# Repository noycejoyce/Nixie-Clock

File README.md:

# Noyce Joyce - Nixie Clock

## PCB design

The printed circuit board was designed in pre-released KiCAD 5.99 available at [nightly build](https://kicad-downloads.s3.cern.ch/index.html?prefix=windows/nightly/).

The core of the board is IoT Bluetooth chip from Nordic Semi nRF52832 which drives Nixie tubes IN-12 statically via nine shift registers.

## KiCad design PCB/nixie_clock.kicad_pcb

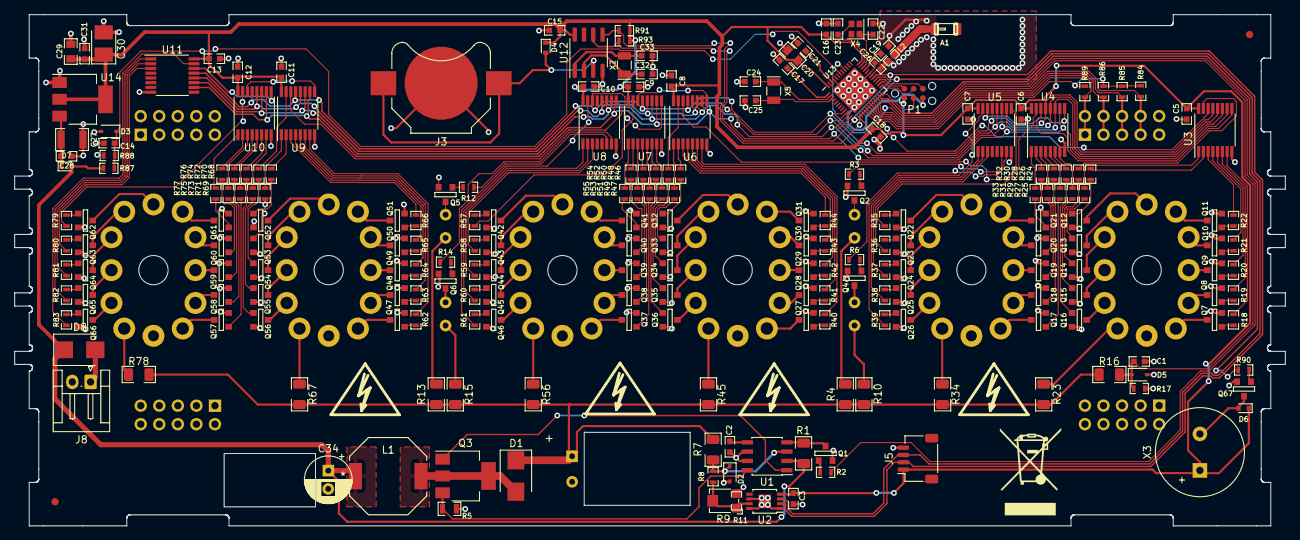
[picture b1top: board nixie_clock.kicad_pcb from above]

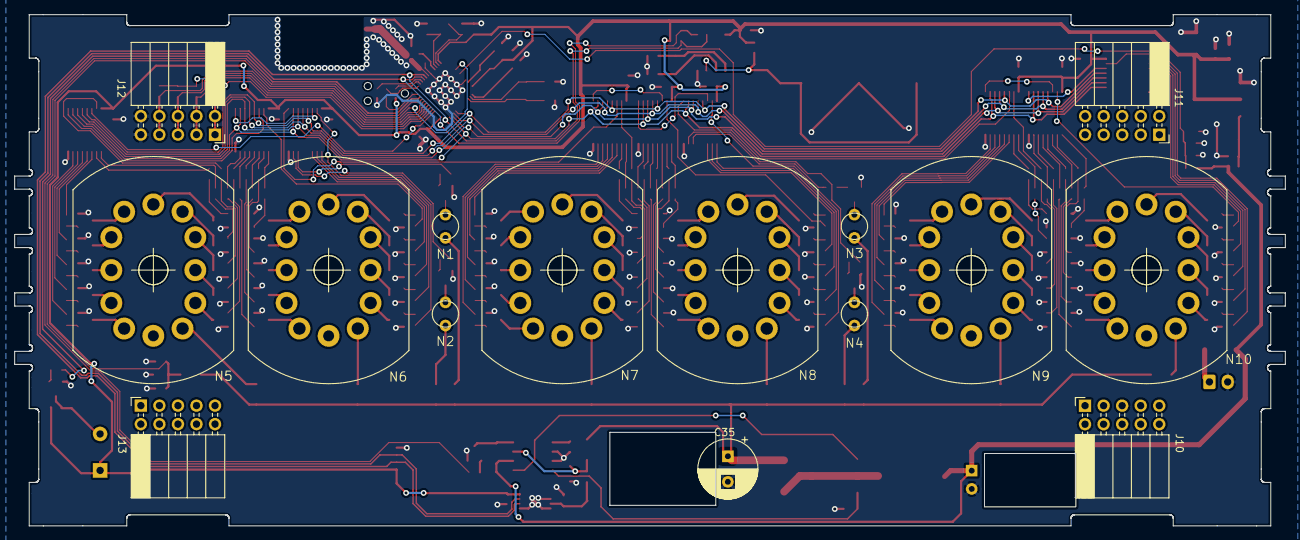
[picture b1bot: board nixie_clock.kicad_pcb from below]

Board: 2 copper layers, 174.0 x 70.0 mm, 247 parts (15 on the bottom side), 258 nets.

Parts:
A1: 2450AT18B100E; 2450A
C1, C2, C3, C5, C6, C7, C8, C9, C10, C11, C12, C13, C14, C17, C28, C31: 100n/50V; C_0603
C15, C16, C18, C21: 1u/25V; C_0603
C19: 100p; C_0603
C20, C29: 22u/6.3V; C_0805
C22, C23, C24, C25, C32, C33: 12p; C_0603
C26: 0.8p; C_0402
C27: 10u/35V; C_1210
C30: 100u/6.3V; CP_Tantalum_Case-B_EIA-3528-21_Reflow
C34: 100u/16V; CP_Radial_D6.3mm_P2.50mm
C35: 2.2u/400V; CP_Radial_D8.0mm_P3.50mm
D1, D8: ES2G; D_SMB_Standard
D2, D3, D5: MM3Z3V3T1G; D_SOD-323
D4, D6, D7: BAT42XV2; D_SOD-523
J1, J2: FiducialMark; AssemblyMark_1.0mm
J3: CR1225; BatteryHolder_Harwin_S8201R_1x12mm
J5: CONN_01X04; JST_SH_SM04B-SRSS-TB_1x04-1MP_P1.00mm_Horizontal
J8: CONN_01X02; JST_EH_S2B-EH_1x02_P2.50mm_Horizontal
J10, J11, J12, J13: CONN_02X05; PinSocket_2x05_P2.54mm_Horizontal
L1: SRU1038-101Y; L_Bourns_SRU1038
L2: 3.9nH; L_0402
N1, N2, N3, N4: IN-3; russian-nixies-IN-6
N5, N6, N7, N8, N9, N10: IN-12A; russian-nixies-IN-12
P1: TC2030-SWD; Tag-Connect_TC2030-IDC-NL
Q1, Q2, Q4, Q5, Q6, Q7, Q8, Q9, Q10, Q11, Q12, Q13, Q14, Q15, Q16, Q17, Q18, Q19, Q20, Q21, Q22, Q23, Q24, Q25, Q26, Q27, Q28, Q29, Q30, Q31, Q32, Q33, Q34, Q35, Q36, Q37, Q38, Q39, Q40, Q41, Q42, Q43, Q44, Q45, Q46, Q47, Q48, Q49, Q50, Q51, Q52, Q53, Q54, Q55, Q56, Q57, Q58, Q59, Q60, Q61, Q62, Q63, Q64, Q65, Q66, Q67: MMBTA42L; SOT-23
Q3: IPN50R1K4CE; SOT-223-3Lead_TabPin2
R1, R7, R16: 1M5; R_1206
R2, R3, R6, R12, R14, R18, R19, R20, R21, R22, R24, R25, R26, R27, R28, R29, R30, R31, R32, R33, R35, R36, R37, R38, R39, R40, R41, R42, R43, R44, R46, R47, R48, R49, R50, R51, R52, R53, R54, R55, R57, R58, R59, R60, R61, R62, R63, R64, R65, R66, R68, R69, R70, R71, R72, R73, R74, R75, R76, R77, R79, R80, R81, R82, R83: 1k; R_0603
R4, R10, R13, R15: 330k; R_1206
R5: 50mR; R_0805
R8, R88: 10k; R_0603
R9: 10k; Potentiometer_Bourns_TC33X_Vertical
R11: 0R; R_0603
R17: 22k; R_0603
R23, R34, R45, R56, R67, R78: 22k; R_1206
R84, R85, R86, R89: 1M; R_0603
R87: 383k; R_0603
R90, R91, R93: 4K7; R_0603
U1: MAX1771; SOIC-8_3.9x4.9mm_Pitch1.27mm
U2: MCP4561; MSOP-8-1EP_3x3mm_Pitch0.65mm
U3, U4, U5, U6, U7, U8, U9, U10, U11: 74HC595; TSSOP-16_4.4x5mm_Pitch0.65mm
U12: MCP7940N; SOIC-8_3.9x4.9mm_P1.27mm
U13: nRF52832; UQFN-48-1EP_6x6mm_Pitch0.4mm
U14: LD1117-3.3; SOT-223-3_TabPin2
X1, X7, X8, X9: High_Voltage; Symbol_HighVoltage_Type2_SilkScreenTop_VerySmall
X2, X5: LFXTAL009678; Crystal_SMD_MicroCrystal_CC7V-T1A-2pin_3.2x1.5mm
X3: SD1209T3-A1; Buzzer_12x9RM5.0
X4: XRCGB32M000; Crystal_SMD_2016-4pin_2.0x1.6mm
X6: Basket; WEEE-Logo_8.4x12mm_SilkScreen

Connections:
3V: C3.1, C5.2, C6.2, C7.2, C8.2, C9.2, C10.2, C11.2, C12.2, C13.2, C15.1, C16.1, C18.1, C20.1, C29.1, C30.1, C31.1, D4.1, D6.1, J5.1, P1.1, R91.1, R93.1, U2.4, U3.16, U4.16, U5.16, U6.16, U7.16, U8.16, U9.16, U10.16, U11.16, U12.8, U13.13, U13.36, U13.48, U14.2, X3.1
+12V: C34.1, D7.2, D8.1, L1.1, R1.1, R87.1, U1.2
/CLK: U3.11, U4.11, U5.11, U6.11, U7.11, U8.11, U9.11, U10.11, U11.11, U13.11
/DATA: U3.14, U13.16
/HIGH_VOLTAGE_EN: R2.1, U13.22
/MCU/BTN_MENU: J12.7, J12.8, R84.2, U13.21
/MCU/BTN_MINUS: J12.5, J12.6, R85.2, U13.20
/MCU/BTN_PLUS: J12.3, J12.4, R86.2, U13.19
/MCU/BTN_SET: J12.1, J12.2, R89.2, U13.18
/MCU/BUZZER: R90.2, U13.23
/MCU/COM_PUSH_BUTTON: R84.1, R85.1, R86.1, R89.1, U13.17
/MCU/RESET: P1.3, U13.24
/MCU/SWCLK: P1.4, U13.25
/MCU/SWDIO: P1.2, U13.26
/MCU/SWO: P1.6, U13.27
/MCU/V_VBUS: C14.1, D3.1, R87.2, R88.1, U13.42
/OE: U3.13, U4.13, U5.13, U6.13, U7.13, U8.13, U9.13, U10.13, U11.13, U13.9
/SCL: J5.2, R93.2, U2.2, U12.6, U13.29
/SDA: J5.3, R91.2, U2.3, U12.5, U13.28
/STCP: U3.12, U4.12, U5.12, U6.12, U7.12, U8.12, U9.12, U10.12, U11.12, U13.10
/V_HV: C1.1, D5.1, R16.2, R17.1, U13.40
/dualDisp2/DATA: U5.9, U6.14
/dualDisp2/Q6: R12.2, U8.6
/dualDisp2/Q7: R14.2, U8.7
/dualDisp3/DATA: U8.9, U9.14
/dualDisplay/Q6: R3.2, U5.6
/dualDisplay/Q7: R6.2, U5.7
/~RST: U3.10, U4.10, U5.10, U6.10, U7.10, U8.10, U9.10, U10.10, U11.10, U13.12
GND: C1.2, C2.2, C3.2, C5.1, C6.1, C7.1, C8.1, C9.1, C10.1, C11.1, C12.1, C13.1, C14.2, C15.2, C16.2, C17.2, C18.2, C19.2, C20.2, C21.2, C22.1, C23.1, C24.1, C25.1, C26.2, C27.2, C28.2, C29.2, C30.2, C31.2, C32.2, C33.2, C34.2, C35.2, D2.2, D3.2, D5.2, J3.2, J5.4, J8.2, J12.9, J12.10, P1.5, Q1.2, Q2.2, Q4.2, Q5.2, Q6.2, Q7.2, Q8.2, Q9.2, Q10.2, Q11.2, Q12.2, Q13.2, Q14.2, Q15.2, Q16.2, Q17.2, Q18.2, Q19.2, Q20.2, Q21.2, Q22.2, Q23.2, Q24.2, Q25.2, Q26.2, Q27.2, Q28.2, Q29.2, Q30.2, Q31.2, Q32.2, Q33.2, Q34.2, Q35.2, Q36.2, Q37.2, Q38.2, Q39.2, Q40.2, Q41.2, Q42.2, Q43.2, Q44.2, Q45.2, Q46.2, Q47.2, Q48.2, Q49.2, Q50.2, Q51.2, Q52.2, Q53.2, Q54.2, Q55.2, Q56.2, Q57.2, Q58.2, Q59.2, Q60.2, Q61.2, Q62.2, Q63.2, Q64.2, Q65.2, Q66.2, Q67.2, R5.2, R9.3, R11.2, R17.2, R88.2, U1.6, U1.7, U2.1, U2.6, U2.8, U2.9, U3.8, U4.8, U5.8, U6.8, U7.8, U8.8, U9.8, U10.8, U11.8, U12.4, U13.31, U13.45, U13.49, U14.1
unnamed: A1.1, L2.2
unnamed: C2.1, U1.5
unnamed: C17.1, U13.1
unnamed: C19.1, U13.33
unnamed: C21.1, U13.46
unnamed: C22.2, U13.34, X4.1
unnamed: C23.2, U13.35, X4.3
unnamed: C24.2, U13.2, X5.1
unnamed: C25.2, U13.3, X5.2
unnamed: C26.1, L2.1, U13.30
unnamed: C27.1, C28.1, D7.1, U14.3
unnamed: C32.1, U12.2, X2.1
unnamed: C33.1, U12.1, X2.2
unnamed: D1.2, L1.2, Q3.2
unnamed: D2.1, R7.2, R8.1, U1.3
unnamed: D4.2, J3.1, U12.3
unnamed: D6.2, Q67.3, X3.2
unnamed: D8.2, J8.1
unnamed: N1.A, R4.2
unnamed: N1.K, Q2.3
unnamed: N2.A, R10.2
unnamed: N2.K, Q4.3
unnamed: N3.A, R13.2
unnamed: N3.K, Q5.3
unnamed: N4.A, R15.2
unnamed: N4.K, Q6.3
unnamed: N5.0, Q16.3
unnamed: N5.1, Q7.3
unnamed: N5.2, Q8.3
unnamed: N5.3, Q9.3
unnamed: N5.4, Q10.3
unnamed: N5.5, Q11.3
unnamed: N5.6, Q12.3
unnamed: N5.7, Q13.3
unnamed: N5.8, Q14.3
unnamed: N5.9, Q15.3
unnamed: N5.A, R23.1
unnamed: N6.0, Q26.3
unnamed: N6.1, Q17.3
unnamed: N6.2, Q18.3
unnamed: N6.3, Q19.3
unnamed: N6.4, Q20.3
unnamed: N6.5, Q21.3
unnamed: N6.6, Q22.3
unnamed: N6.7, Q23.3
unnamed: N6.8, Q24.3
unnamed: N6.9, Q25.3
unnamed: N6.A, R34.1
unnamed: N7.0, Q36.3
unnamed: N7.1, Q27.3
unnamed: N7.2, Q28.3
unnamed: N7.3, Q29.3
unnamed: N7.4, Q30.3
unnamed: N7.5, Q31.3
unnamed: N7.6, Q32.3
unnamed: N7.7, Q33.3
unnamed: N7.8, Q34.3
unnamed: N7.9, Q35.3
unnamed: N7.A, R45.1
unnamed: N8.0, Q46.3
unnamed: N8.1, Q37.3
unnamed: N8.2, Q38.3
unnamed: N8.3, Q39.3
unnamed: N8.4, Q40.3
unnamed: N8.5, Q41.3
unnamed: N8.6, Q42.3
unnamed: N8.7, Q43.3
unnamed: N8.8, Q44.3
unnamed: N8.9, Q45.3
unnamed: N8.A, R56.1
unnamed: N9.0, Q56.3
unnamed: N9.1, Q47.3
unnamed: N9.2, Q48.3
unnamed: N9.3, Q49.3
unnamed: N9.4, Q50.3
unnamed: N9.5, Q51.3
unnamed: N9.6, Q52.3
unnamed: N9.7, Q53.3
unnamed: N9.8, Q54.3
unnamed: N9.9, Q55.3
unnamed: N9.A, R67.1
unnamed: N10.0, Q66.3
unnamed: N10.1, Q57.3
unnamed: N10.2, Q58.3
unnamed: N10.3, Q59.3
unnamed: N10.4, Q60.3
unnamed: N10.5, Q61.3
unnamed: N10.6, Q62.3
unnamed: N10.7, Q63.3
unnamed: N10.8, Q64.3
unnamed: N10.9, Q65.3
unnamed: N10.A, R78.1
unnamed: Q1.1, R2.2
unnamed: Q1.3, R1.2, U1.4
unnamed: Q2.1, R3.1
unnamed: Q3.1, U1.1
unnamed: Q3.3, R5.1, U1.8
unnamed: Q4.1, R6.1
unnamed: Q5.1, R12.1
unnamed: Q6.1, R14.1
unnamed: Q7.1, R18.1
unnamed: Q8.1, R19.1
unnamed: Q9.1, R20.1
unnamed: Q10.1, R21.1
unnamed: Q11.1, R22.1
unnamed: Q12.1, R24.1
unnamed: Q13.1, R25.1
unnamed: Q14.1, R26.1
unnamed: Q15.1, R27.1
unnamed: Q16.1, R28.1
unnamed: Q17.1, R29.1
unnamed: Q18.1, R30.1
unnamed: Q19.1, R31.1
unnamed: Q20.1, R32.1
unnamed: Q21.1, R33.1
unnamed: Q22.1, R35.1
unnamed: Q23.1, R36.1
unnamed: Q24.1, R37.1
unnamed: Q25.1, R38.1
unnamed: Q26.1, R39.1
unnamed: Q27.1, R40.1
unnamed: Q28.1, R41.1
unnamed: Q29.1, R42.1
unnamed: Q30.1, R43.1
unnamed: Q31.1, R44.1
unnamed: Q32.1, R46.1
unnamed: Q33.1, R47.1
unnamed: Q34.1, R48.1
unnamed: Q35.1, R49.1
unnamed: Q36.1, R50.1
unnamed: Q37.1, R51.1
unnamed: Q38.1, R52.1
unnamed: Q39.1, R53.1
unnamed: Q40.1, R54.1
unnamed: Q41.1, R55.1
unnamed: Q42.1, R57.1
unnamed: Q43.1, R58.1
unnamed: Q44.1, R59.1
unnamed: Q45.1, R60.1
unnamed: Q46.1, R61.1
unnamed: Q47.1, R62.1
unnamed: Q48.1, R63.1
unnamed: Q49.1, R64.1
unnamed: Q50.1, R65.1
unnamed: Q51.1, R66.1
unnamed: Q52.1, R68.1
unnamed: Q53.1, R69.1
unnamed: Q54.1, R70.1
unnamed: Q55.1, R71.1
unnamed: Q56.1, R72.1
unnamed: Q57.1, R73.1
unnamed: Q58.1, R74.1
unnamed: Q59.1, R75.1
unnamed: Q60.1, R76.1
unnamed: Q61.1, R77.1
unnamed: Q62.1, R79.1
unnamed: Q63.1, R80.1
unnamed: Q64.1, R81.1
unnamed: Q65.1, R82.1
unnamed: Q66.1, R83.1
unnamed: Q67.1, R90.1
unnamed: R8.2, R9.1, R9.2, R11.1, U2.7
unnamed: R18.2, U3.7
unnamed: R19.2, U3.6
unnamed: R20.2, U3.5
unnamed: R21.2, U3.4
unnamed: R22.2, U3.3
unnamed: R24.2, U3.2
unnamed: R25.2, U3.1
unnamed: R26.2, U3.15
unnamed: R27.2, U4.7
unnamed: R28.2, U4.6
unnamed: R29.2, U4.5
unnamed: R30.2, U4.4
unnamed: R31.2, U4.3
unnamed: R32.2, U4.2
unnamed: R33.2, U4.1
unnamed: R35.2, U4.15
unnamed: R36.2, U5.3
unnamed: R37.2, U5.2
unnamed: R38.2, U5.1
unnamed: R39.2, U5.15
unnamed: R40.2, U6.7
unnamed: R41.2, U6.6
unnamed: R42.2, U6.5
unnamed: R43.2, U6.4
unnamed: R44.2, U6.3
unnamed: R46.2, U6.2
unnamed: R47.2, U6.1
unnamed: R48.2, U6.15
unnamed: R49.2, U7.7
unnamed: R50.2, U7.6
unnamed: R51.2, U7.5
unnamed: R52.2, U7.4
unnamed: R53.2, U7.3
unnamed: R54.2, U7.2
unnamed: R55.2, U7.1
unnamed: R57.2, U7.15
unnamed: R58.2, U8.3
unnamed: R59.2, U8.2
unnamed: R60.2, U8.1
unnamed: R61.2, U8.15
unnamed: R62.2, U9.7
unnamed: R63.2, U9.6
unnamed: R64.2, U9.5
unnamed: R65.2, U9.4
unnamed: R66.2, U9.3
unnamed: R68.2, U9.2
unnamed: R69.2, U9.1
unnamed: R70.2, U9.15
unnamed: R71.2, U10.7
unnamed: R72.2, U10.6
unnamed: R73.2, U10.5
unnamed: R74.2, U10.4
unnamed: R75.2, U10.3
unnamed: R76.2, U10.2
unnamed: R77.2, U10.1
unnamed: R79.2, U10.15
unnamed: R80.2, U11.3
unnamed: R81.2, U11.2
unnamed: R82.2, U11.1
unnamed: R83.2, U11.15
unnamed: U3.9, U4.14
unnamed: U4.9, U5.14
unnamed: U6.9, U7.14
unnamed: U7.9, U8.14
unnamed: U10.9, U11.14
unnamed: U9.9, U10.14
VHV: C35.1, D1.1, R4.1, R7.1, R10.1, R13.1, R15.1, R16.1, R23.2, R34.2, R45.2, R56.2, R67.2, R78.2

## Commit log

2021-04-12 initial version
